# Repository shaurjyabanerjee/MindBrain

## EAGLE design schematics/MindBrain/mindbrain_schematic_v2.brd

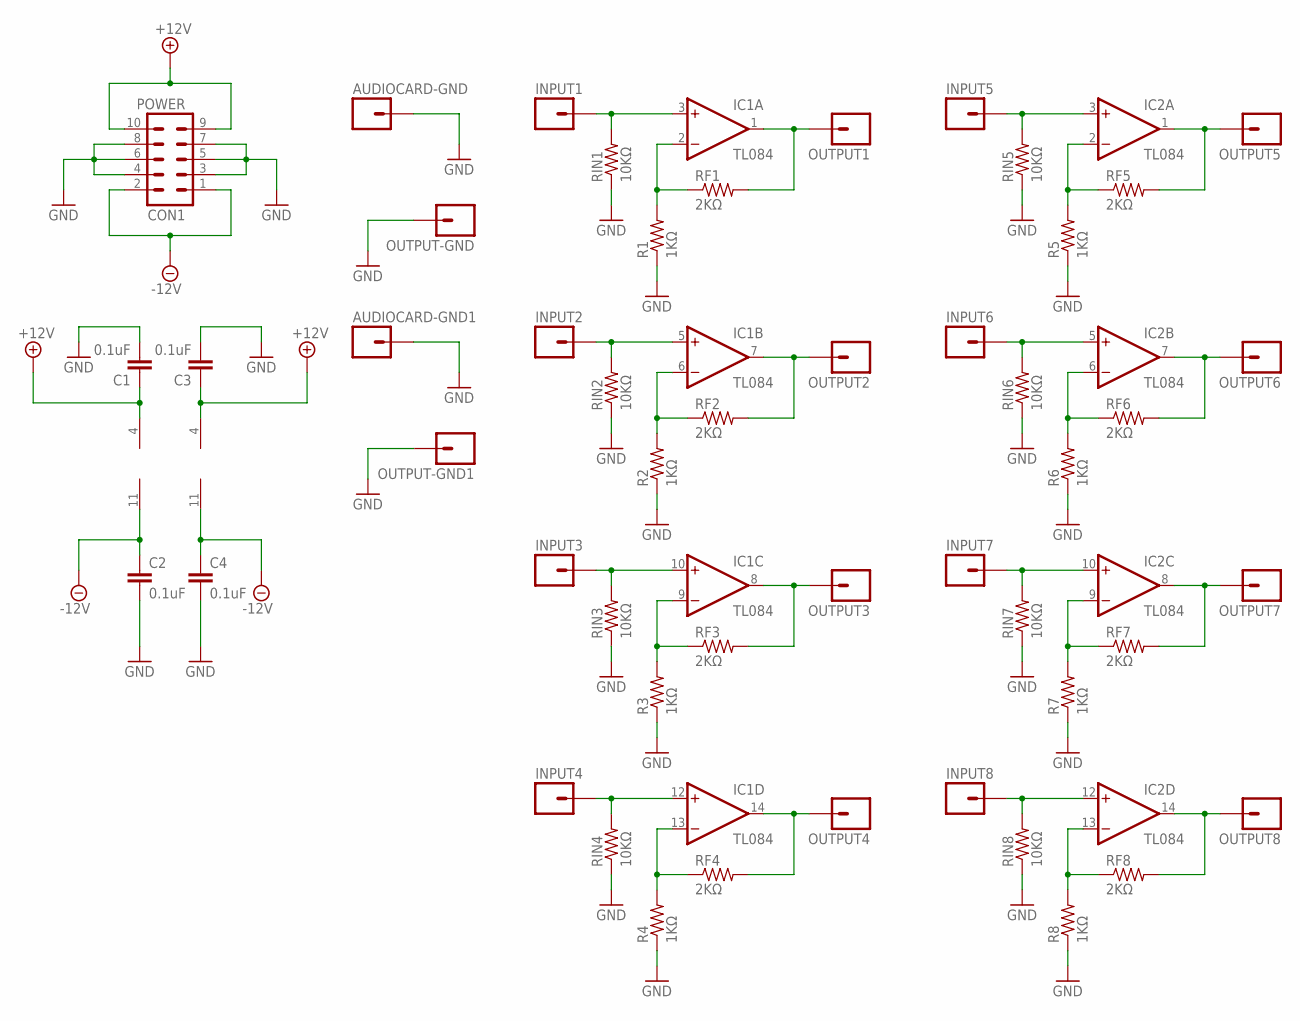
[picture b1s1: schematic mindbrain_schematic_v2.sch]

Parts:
AUDIOCARD-GND, AUDIOCARD-GND1: M01NOSILK-KIT; 1X01NS-KIT
C1, C2, C3, C4: 0.1uF; CAP-PTH-SMALL-KIT
CON1: POWER; 2X5-SHROUDED
IC1, IC2: TL084; DIL14
INPUT1, INPUT2, INPUT3, INPUT4, INPUT5, INPUT6, INPUT7, INPUT8: M01NOSILK-KIT; 1X01NS-KIT
OUTPUT1, OUTPUT2, OUTPUT3, OUTPUT4, OUTPUT5, OUTPUT6, OUTPUT7, OUTPUT8: M01NOSILK-KIT; 1X01NS-KIT
OUTPUT-GND, OUTPUT-GND1: M01NOSILK-KIT; 1X01NS-KIT
R1, R2, R3, R4, R5, R6, R7, R8: 1KΩ; AXIAL-0.4
RF1, RF2, RF3, RF4, RF5, RF6, RF7, RF8: 2KΩ; AXIAL-0.4
RIN1, RIN2, RIN3, RIN4, RIN5, RIN6, RIN7, RIN8: 10KΩ; AXIAL-0.4

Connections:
+12V: C1.1, C3.1, CON1.9, CON1.10, IC1.4 (V+), IC2.4 (V+)
-12V: C2.1, C4.1, CON1.1, CON1.2, IC1.11 (V-), IC2.11 (V-)
GND: AUDIOCARD-GND.1, AUDIOCARD-GND1.1, C1.2, C2.2, C3.2, C4.2, CON1.3, CON1.4, CON1.5, CON1.6, CON1.7, CON1.8, OUTPUT-GND.1, OUTPUT-GND1.1, R1.P$1 (1), R2.P$1 (1), R3.P$1 (1), R4.P$1 (1), R5.P$1 (1), R6.P$1 (1), R7.P$1 (1), R8.P$1 (1), RIN1.P$1 (1), RIN2.P$1 (1), RIN3.P$1 (1), RIN4.P$1 (1), RIN5.P$1 (1), RIN6.P$1 (1), RIN7.P$1 (1), RIN8.P$1 (1)
unnamed: IC1.3 (+IN), INPUT1.1, RIN1.P$2 (2)
unnamed: IC1.1 (OUT), OUTPUT1.1, RF1.P$2 (2)
unnamed: IC1.2 (-IN), R1.P$2 (2), RF1.P$1 (1)
unnamed: IC1.5 (+IN), INPUT2.1, RIN2.P$2 (2)
unnamed: IC1.7 (OUT), OUTPUT2.1, RF2.P$2 (2)
unnamed: IC1.6 (-IN), R2.P$2 (2), RF2.P$1 (1)
unnamed: IC1.10 (+IN), INPUT3.1, RIN3.P$2 (2)
unnamed: IC1.8 (OUT), OUTPUT3.1, RF3.P$2 (2)
unnamed: IC1.9 (-IN), R3.P$2 (2), RF3.P$1 (1)
unnamed: IC1.12 (+IN), INPUT4.1, RIN4.P$2 (2)
unnamed: IC1.14 (OUT), OUTPUT4.1, RF4.P$2 (2)
unnamed: IC1.13 (-IN), R4.P$2 (2), RF4.P$1 (1)
unnamed: IC2.3 (+IN), INPUT5.1, RIN5.P$2 (2)
unnamed: IC2.1 (OUT), OUTPUT5.1, RF5.P$2 (2)
unnamed: IC2.2 (-IN), R5.P$2 (2), RF5.P$1 (1)
unnamed: IC2.5 (+IN), INPUT6.1, RIN6.P$2 (2)
unnamed: IC2.7 (OUT), OUTPUT6.1, RF6.P$2 (2)
unnamed: IC2.6 (-IN), R6.P$2 (2), RF6.P$1 (1)
unnamed: IC2.10 (+IN), INPUT7.1, RIN7.P$2 (2)
unnamed: IC2.8 (OUT), OUTPUT7.1, RF7.P$2 (2)
unnamed: IC2.9 (-IN), R7.P$2 (2), RF7.P$1 (1)
unnamed: IC2.12 (+IN), INPUT8.1, RIN8.P$2 (2)
unnamed: IC2.14 (OUT), OUTPUT8.1, RF8.P$2 (2)
unnamed: IC2.13 (-IN), R8.P$2 (2), RF8.P$1 (1)

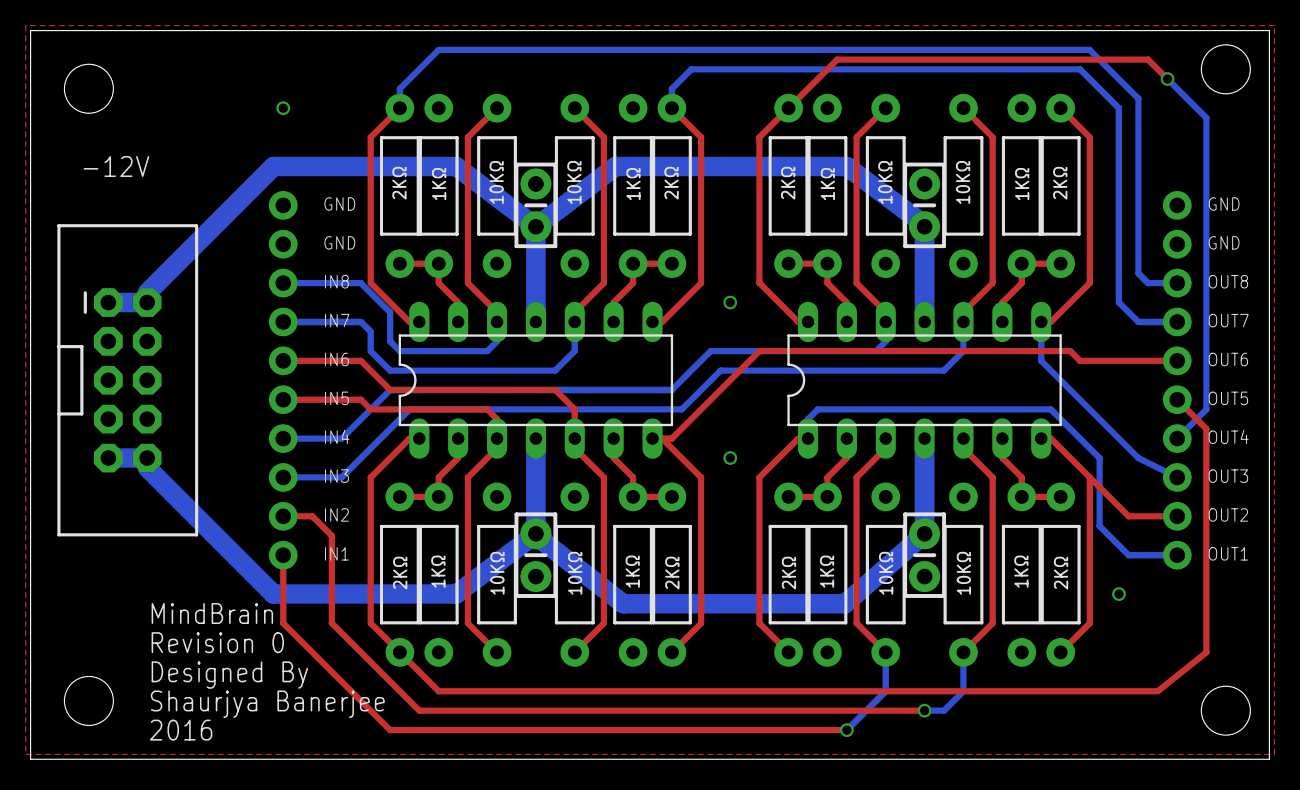
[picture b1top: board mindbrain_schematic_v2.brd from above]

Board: 2 copper layers, 81.0 x 47.6 mm, 51 parts (0 on the bottom side), 27 nets.

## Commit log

2016-06-26 updated file structure
2016-06-27 added schematics folder
2016-06-27 example commit
2016-06-28 added artwork assests
2016-06-29 added dual function generator
2016-06-29 added logo to pitch tools
2016-06-29 added logos to modulation tools
2016-06-29 added artwork to all UIs
2016-06-29 fixed naming and logo spacing of envelope generator
2016-06-29 added first lit up logo option
2016-06-29 glowing brain test
2016-06-29 added lower res logos
2016-06-29 fixed loading bug/added envelope reactive glow
2016-06-30 changed glow colour/loadbug fix
2016-06-30 UI changes for random gen
2016-06-30 added dual LFO/UI Changes
2016-06-30 dual lfo added
2016-06-30 added artwork AutoCAD files to repo
2016-07-01 fixed missing connections in Pitch_Tools
2016-07-01 driver name override PLIST hack
2016-07-01 added terminal commands list for driver override
2016-07-03 added refactor list text file
2016-07-04 UI glow added to Pitch_Tools/Fixed gate bug, scaling from -1. - 1. now.
2016-07-04 bug fixes to pitch_tools
2016-07-04 ui freezed
2016-07-04 UI updates for pitch tools
2016-07-04 adding time_tools folder
2016-07-04 added MIDI to trigger, for reals
2016-07-04 removed dummy text file
2016-07-04 patch clean up
2016-07-04 random gen clean up + bug fix on Load
2016-07-04 refactor list updated, have a look!
2016-07-04 added background panels to pitch_tools
2016-07-04 added panels to all UIs, and fixed device widths
2016-07-04 created board files in Eagle, started layout
2016-07-04 fixed component designator confusion
2016-07-04 completed basic board placement
2016-07-04 connected power supply grounds to circuit ground
2016-07-04 made connections to bypass caps in schematic view
2016-07-04 placed bypass caps in board view
2016-07-04 added epf file (not sure what that is?)
2016-07-05 started laying traces, top side
2016-07-05 updated top layer layouts
2016-07-05 replaced ground traces with ground pour
2016-07-05 not so sure about ground pour. Going back to airwired grounds for now
2016-07-05 added audio input and output grounds
2016-07-05 trying new style board layout, flippinng orientation of feedback and input resistors
2016-07-05 layed out non io/pwr/gnd traces
2016-07-05 layed out input traces for channels 5, 6, 7, 8
2016-07-05 layed out all input traces
2016-07-05 added ground pour
2016-07-05 routed +/- power bottomside
2016-07-06 started v2 board layout. Tying some new trix
2016-07-06 trying to split traces between top and bottom layers
2016-07-06 morseTrigger Prototype added to /time_tools
2016-07-06 enter to start sequence added
2016-07-06 Got all traces except gnds using vias
2016-07-06 trying to fix merge conflicts
2016-07-06 hopefully this is how the repo should look?
2016-07-06 removed redundant top layer silkscreen for component designators
2016-07-06 centered silkscreen on component footprints
2016-07-06 added top and bottom ground pours + revision silkscreen
2016-07-06 added vias joining top and bottom ground pours
2016-07-06 getting ERC warnings, not sure why?
2016-07-06 Morse Trigger, with Enter to trigger! Clean up
2016-07-06 added input and output silkscreen
2016-07-06 cleaned up schematic thx nathan
2016-07-06 Passing DRC and ERC!!!
2016-07-06 redid i/o silkscreen
2016-07-07 preset management
2016-07-07 widened input power traces ala nathan
2016-07-08 AutoMapping added for Random Gen. Env Gen patch clean up, bug fix and automapping. Added playhead for to Env gen
2016-07-09 added mounting holes, modified silkscreen
2016-07-09 added manufacturing details folder
2016-07-09 added gerber files and CAM job file
2016-07-09 passing SeeedStudio DRC
2016-07-09 added details for seeedstudio and pcbway manufacturing costs
2016-07-09 updated refactor list, pitch tracker bug
2016-07-10 morse code with cool UI
2016-07-16 added monochrome logo for PCB rev1
2016-08-12 Added Polyphonic capabilites and voice allocator. Bug fixes
2016-08-15 Delete MindBrain.PitchGate||EnvOut.amxd
    deleted old version of pitch-gateout
2016-08-15 updated UX with new fonts for time tools and env
2016-08-15 updated fonts of modulation tools and time tools
2016-08-15 updated all UIs except pitch out and voice allocator
2016-08-16 added poly pitch tools
2016-08-16 refactor list changed
2016-08-17 UI and Patch Clean up
2016-08-18 intercommunication for poly instances fixed
2016-08-18 added range limiting to midi->trigger
2016-08-18 added tracking thresholds to the pitch calibrator
2016-08-23 adsr arrives
2016-08-23 added bottom thresh for adsr time
2016-08-23 poly availibility added to all modes! the future is now, the future is reich!
2016-08-23 euclidean sequencer added
2016-08-23 pitch UI changed fam
2016-08-23 deleted old pitch gate env out
2016-08-23 deleted old voice allocator
2016-08-23 refactor list
2016-08-23 fixed freeze issue with new pitch out
2016-08-23 fixed pitch tools UIs pt.1
2016-08-23 updated UI for dual random generator
2016-08-24 added knobs to pitch device
2016-08-24 inverted release knob feedback
2016-08-25 UI changes for pitch tools
2016-08-25 UI changes continues
2016-08-25 i heard you like UI changes...
2016-08-25 so here are some more UI changes
2016-08-25 renamed pitch out
2016-08-25 rename and delete pitch-gate-env-poly
2016-09-01 UI changes pt IV
2016-09-05 Locked and loaded!
2016-09-05 added gerber files for all 3 rev1 PCBs
2016-09-16 added spawn functionality to the euclidean seq

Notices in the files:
parts and their libraries:
SparkFun-Connectors: Licensing: Creative Commons ShareAlike 4.0 International - https://creativecommons.org/licenses/by-sa/4.0
